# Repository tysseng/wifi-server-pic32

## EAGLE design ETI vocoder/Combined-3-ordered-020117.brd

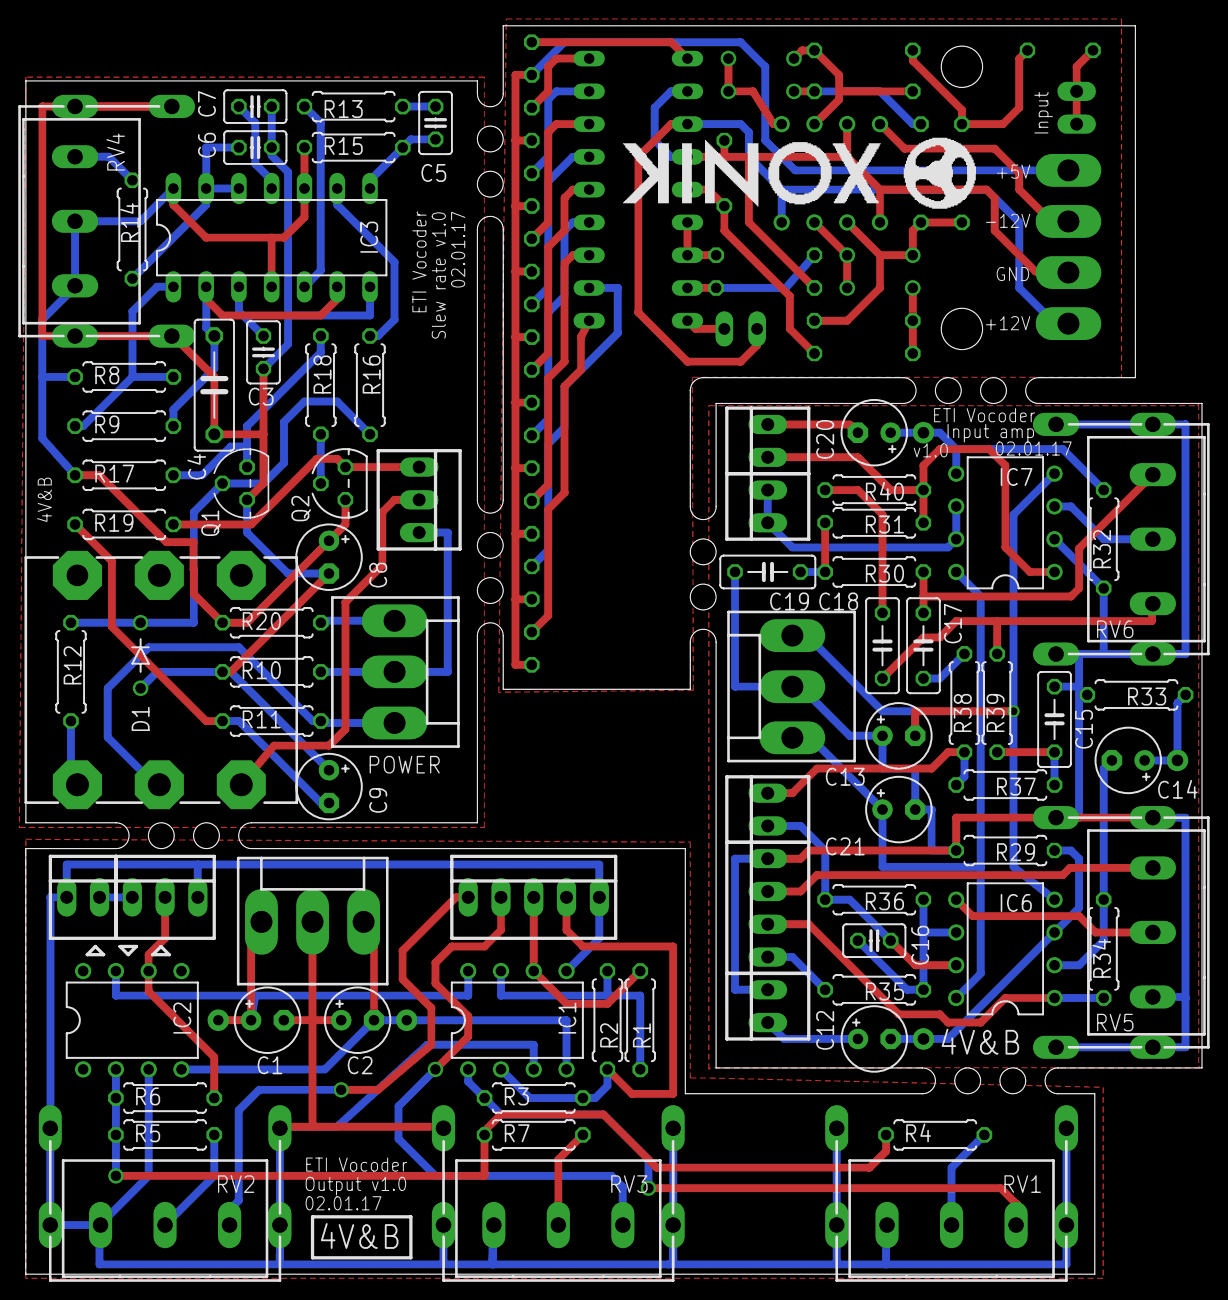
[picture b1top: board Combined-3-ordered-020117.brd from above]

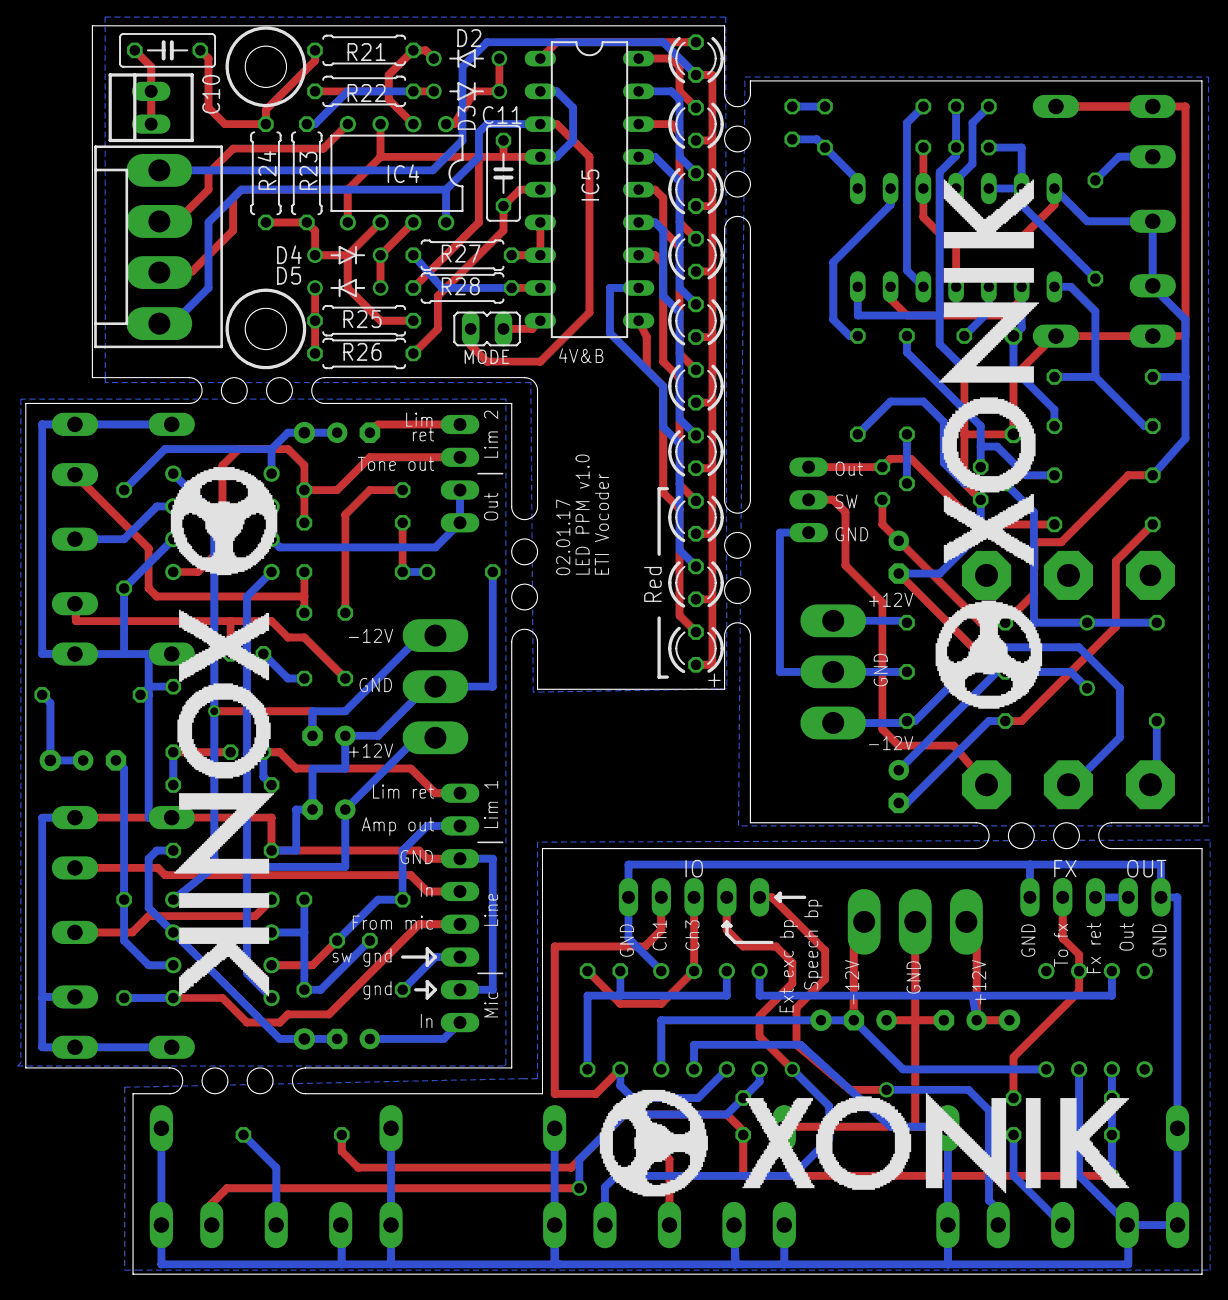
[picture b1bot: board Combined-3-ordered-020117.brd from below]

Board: 2 copper layers, 91.2 x 96.8 mm, 107 parts (29 on the bottom side), 88 nets.

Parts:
C1, C2: 1uF; E2,5-5
C3, C7: 10n; C025-025X050
C4: 33n; C075-032X103
C5: 100p; C025-025X050
C6: 560p; C025-025X050
C8, C9, C14: 22u; E2,5-5
C10, C15, C19: 220n; C050-025X075
C11: 470n; C050-025X075
C12, C20: 1u; E2,5-5
C13, C21: 22u/25V; E2,5-5
C16: 68p; C025-025X050
C17, C18: 2n2; C050-025X075
CN1: NMJ6HCD2
D1: 1N4148; DO35-5J
D2, D3, D4, D5: 1N4148DOJ35-5; DO35-5J
IC1, IC7: LM1458N; DIL08
IC2: LM741P; DIL08
IC3: LM556N; DIL14
IC4: TL082P; DIL08
IC5: LM3915N; DIL18
IC6: LM4558N; DIL08
IN: 22-23-2021
J1: 22-23-2031
LED1, LED2, LED3, LED4, LED5, LED6, LED7, LED8, LED9, LED10: LED3MM
LIM1, LIM2: 22-23-2021
LINE: 22-23-2041
MIC: 22-23-2021
MODE: JP1
OUT: 22-23-2021
POWER, POWER2: KK-156-3
POWER1: KK-156-4
Q1: 2N3904; TO92
Q2: 2N3906; TO92
R1, R2, R4, R5, R6, R7, R34: 22k; 0207/7
R3: 33k; 0207/7
R8: 15k; 0207/7
R9, R14, R17, R19: 2k2; 0207/7
R10, R20: 47R; 0207/7
R11: 220R; 0207/7
R12: 470R; 0207/7
R13, R26: 1k; 0207/7
R15, R16, R18: 10k; 0207/7
R21, R22, R23, R29, R32, R36: 100k; 0207/7
R24, R25: 200k; 0207/7
R27: 680R; 0207/7
R28: 150R; 0207/7
R30, R39: 47k; 0207/7
R31, R37: 1k5; 0207/7
R33: 470R/5k6; 0207/7
R35: 11k; 0207/7
R38, R40: 51k; 0207/7
RV1, RV2, RV3, RV5: 10k log; POT16_W_BRACKET
RV4: 1M log; POT16_W_BRACKET
RV6: 47k lin; POT16_W_BRACKET
X1: KK-156-3
X2: 22-23-2051
X3: 22-23-2021
X4: 22-23-2031

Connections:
0V: C3.1, C4.2, C6.1, C7.2, C8.-, C9.+, D1.A, IC3.7, Q1.3, R10.1, RV4.M1, RV4.M2, RV4.M3, RV4.M4
+5V: LED1.A, LED2.A, LED3.A, LED4.A, LED5.A, LED6.A, LED7.A, LED8.A, LED9.A, LED10.A, POWER1.4
+11V: C8.+, IC3.4, IC3.10, IC3.14, Q2.3, R8.2, R15.1, R17.2, R20.1, RV4.1E, RV4.1S
+12V: C1.+, IC1.8, IC2.7, X1.1
+12V1: POWER.1, R20.2
+12V2: IC4.8, IC5.3, MODE.2, POWER1.1
+12V3: C21.+, IC6.8, IC7.8, POWER2.1
-11V: C9.-, R11.1, R19.2
-12V: C2.-, IC1.4, IC2.4, X1.3
-12V1: CN1.R, POWER.3, R11.2
-12V2: IC4.4, POWER1.3
-12V3: C13.-, IC6.4, IC7.4, POWER2.3
AMP_OUT: C16.2, IC6.7, LIM1.1, R36.2
BUFFER_IN: C20.-, LIM2.2
CH1-2-4: IC1.2, R2.2, R3.1, X2.4
CH3-5-7: IC1.6, R1.1, X2.3
EXT_EXCIT: RV3.1E, X2.2
FROM_V/UV_SWITCH: CN1.T, X4.2
FX_RETURN: J1.1, X3.2
GND: C1.-, C2.+, IC1.3, IC1.5, IC2.3, J1.3, RV1.1A, RV1.M1, RV1.M2, RV1.M3, RV1.M4, RV2.1A, RV2.M1, RV2.M2, RV2.M3, RV2.M4, RV3.1A, RV3.M1, RV3.M2, RV3.M3, RV3.M4, X1.2, X2.5, X3.1
GND1: POWER.2, R10.2, X4.3
GND2: C11.1, IC4.3, IC4.5, IC5.2, IC5.4, POWER1.2, R28.1
GND3: C13.+, C15.2, C19.1, C21.-, IC7.2, LINE.4, MIC.2, POWER2.2, R29.1, R32.1, R33.1, RV5.1A, RV5.M1, RV5.M2, RV5.M3, RV5.M4, RV6.M1, RV6.M2, RV6.M3, RV6.M4
LINE_IN: LINE.3, RV5.1E
MIC_IN: C12.+, MIC.1
MIC_OUT: IC6.1, LINE.2, R34.1
MIX: IC2.6, J1.2, R6.2
MODE: IC5.9, MODE.1
unnamed: R4.1, RV1.1S
unnamed: C5.2, IC3.8, R15.2
unnamed: IC1.7, R1.2, R2.1
unnamed: C4.1, IC3.2, IC3.6, R9.2
unnamed: C7.1, IC3.11
unnamed: IC1.1, R3.2, RV1.1E
unnamed: R7.1, RV3.1S
unnamed: IC2.2, R4.2, R5.1, R6.1, R7.2
unnamed: IC3.9, R16.1
unnamed: R5.2, RV2.1S
unnamed: C6.2, IC3.12, IC3.13, R14.1
unnamed: C5.1, R13.2
unnamed: IC3.5, R13.1
unnamed: IC3.1, R8.1, R9.1
unnamed: R14.2, RV4.1A
unnamed: C3.2, IC3.3
unnamed: D1.C, Q1.2, R12.2, R16.2
unnamed: Q1.1, R17.1, R18.2
unnamed: Q2.2, R18.1
unnamed: CN1.S, R12.1
unnamed: D3.A, R22.1, R23.2
unnamed: D2.C, IC4.2, R21.1, R22.2
unnamed: D2.A, D3.C, IC4.1
unnamed: D4.A, IC4.6, R23.1, R24.1, R25.2
unnamed: D5.C, R25.1, R26.1
unnamed: C10.2, R21.2, R24.2
unnamed: D4.C, D5.A, IC4.7
unnamed: C11.2, IC5.5, R26.2
unnamed: IC5.6, IC5.7, R27.2
unnamed: IC5.1, LED1.K
unnamed: IC5.18, LED2.K
unnamed: IC5.17, LED3.K
unnamed: IC5.16, LED4.K
unnamed: IC5.15, LED5.K
unnamed: IC5.14, LED6.K
unnamed: IC5.13, LED7.K
unnamed: IC5.12, LED8.K
unnamed: IC5.11, LED9.K
unnamed: IC5.10, LED10.K
unnamed: C10.1, IN.1, IN.2
unnamed: IC5.8, R27.1, R28.2
unnamed: C12.-, IC6.3, R29.2
unnamed: C14.-, IC6.2, R34.2
unnamed: C14.+, R33.2
unnamed: C16.1, IC6.6, R35.2, R36.1
unnamed: C15.1, R37.2, R39.2
unnamed: C18.1, R39.1, RV6.1A
unnamed: C17.2, R30.1, RV6.1E
unnamed: C17.1, R38.2
unnamed: C18.2, R40.1
unnamed: C19.2, R30.2, R31.1
unnamed: C20.+, IC7.5, R32.2
unnamed: IC7.3, RV6.1S
unnamed: IC6.5, RV5.1S
OUT: Q2.1, R19.1, X4.1
OUT1: IC7.6, IC7.7, OUT.1, OUT.2
SPEECH: RV2.1E, X2.1
SWITCHED_GND: LINE.1, R35.1
TONE_IN: LIM1.2, R37.1, R38.1
TONE_OUT: IC7.1, LIM2.1, R31.2, R40.2

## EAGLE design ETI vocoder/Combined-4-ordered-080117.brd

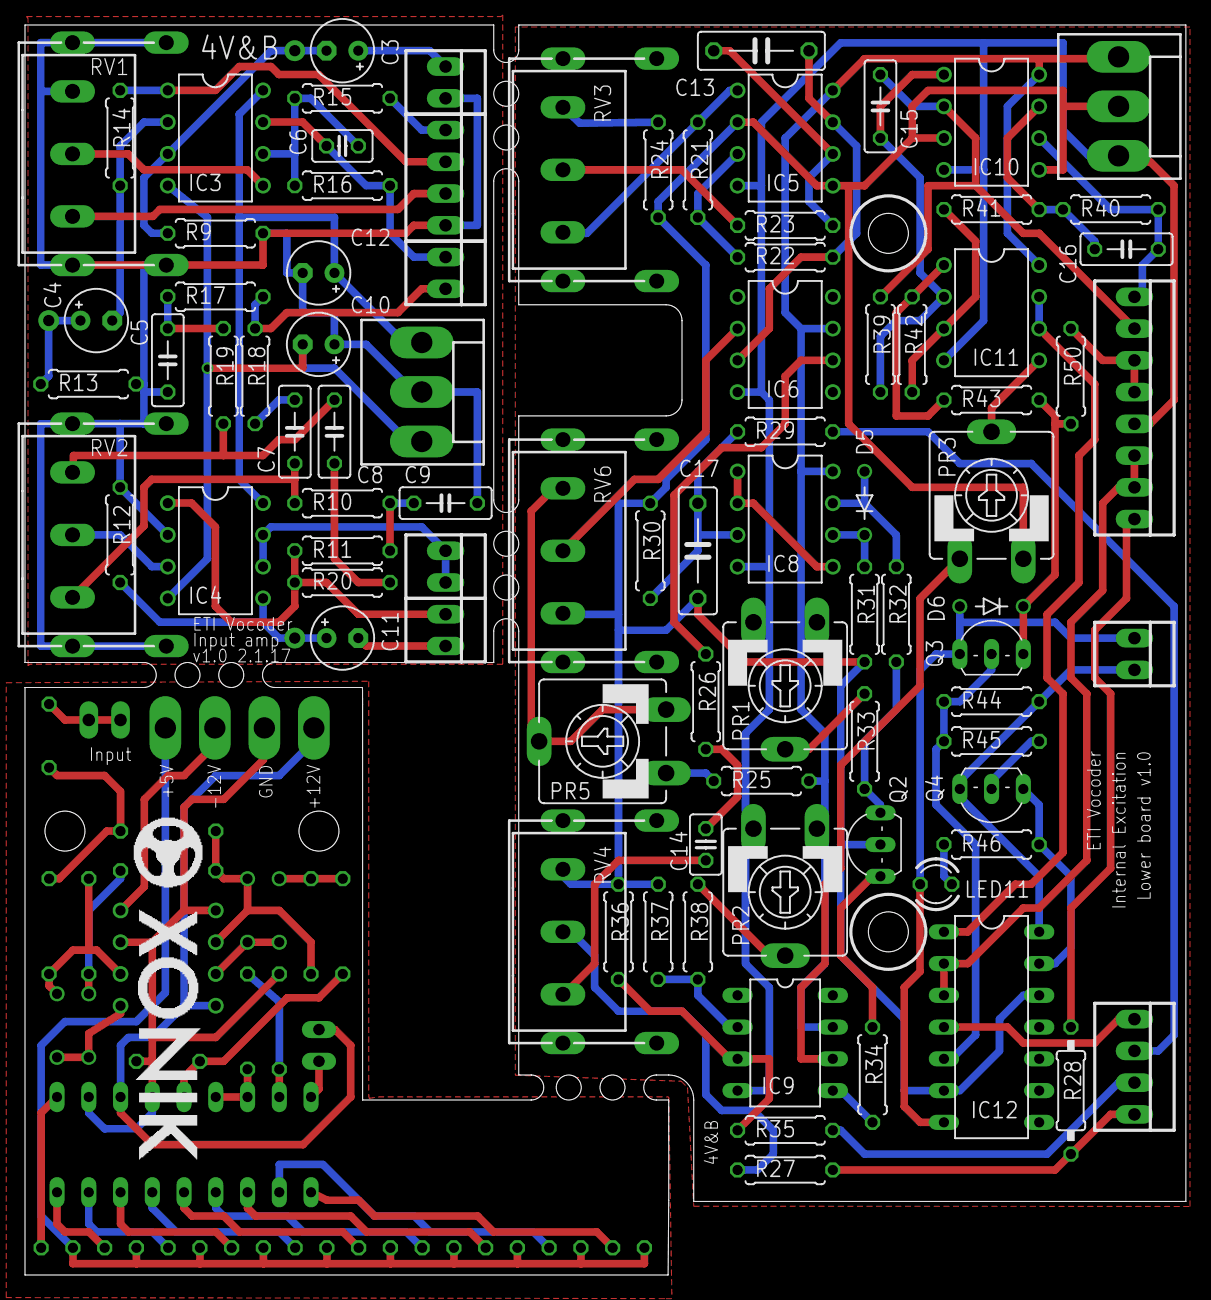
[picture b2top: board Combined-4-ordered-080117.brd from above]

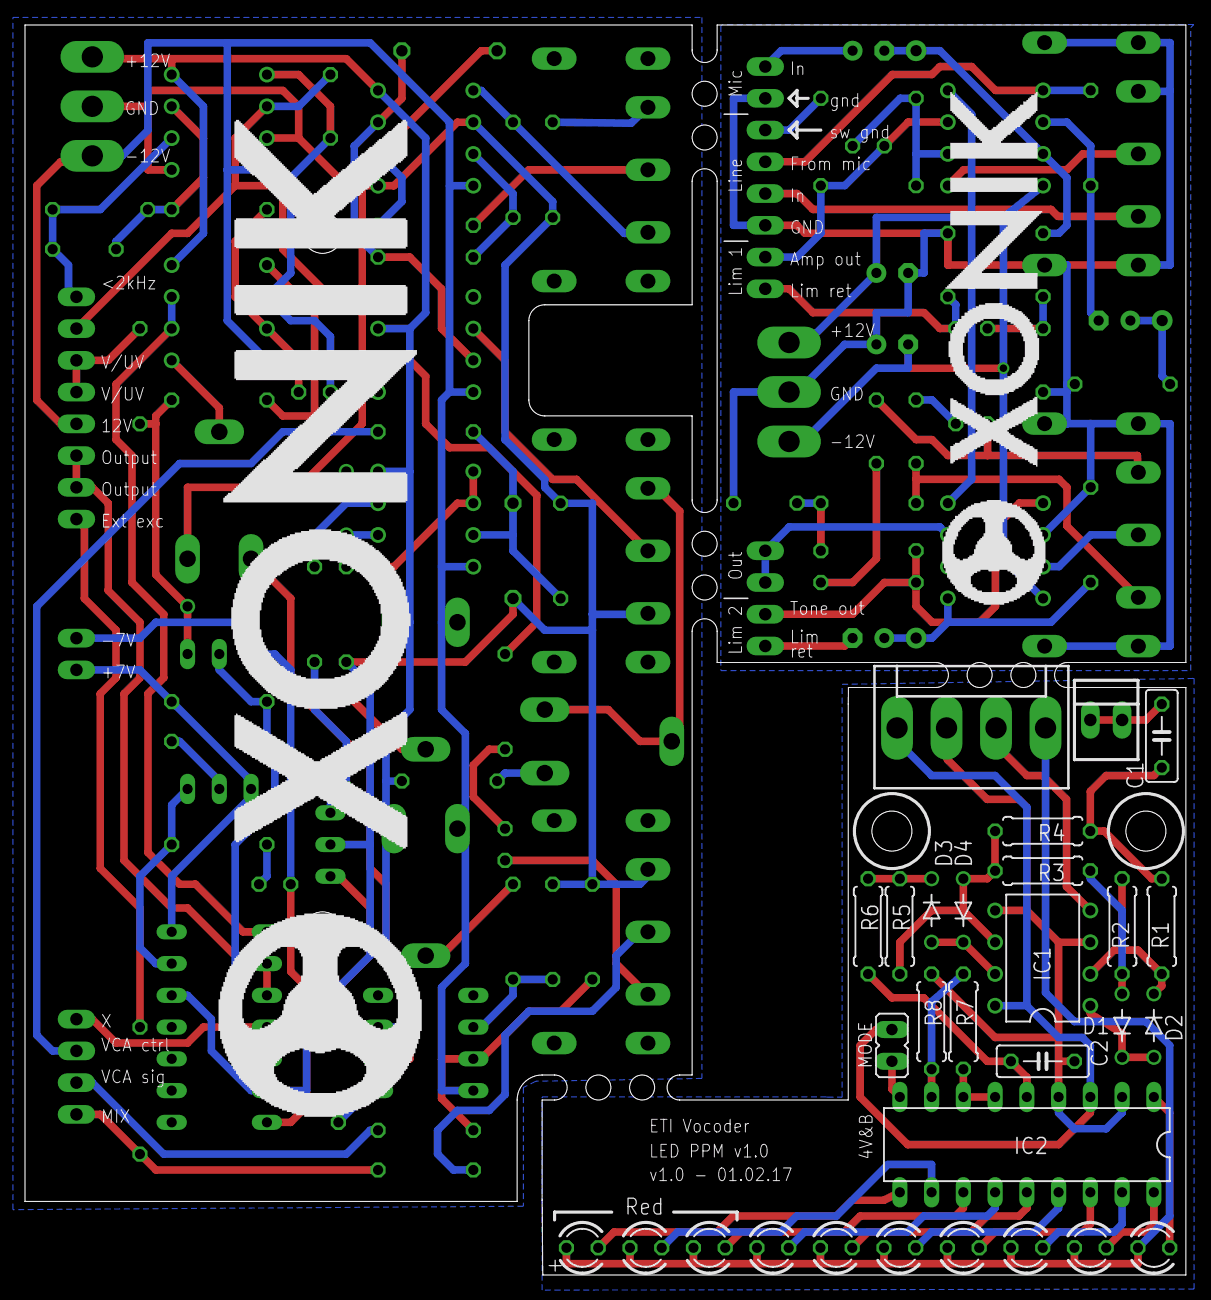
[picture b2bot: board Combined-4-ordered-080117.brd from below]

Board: 2 copper layers, 92.9 x 100.0 mm, 117 parts (29 on the bottom side), 101 nets.

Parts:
BOARD2: 22-23-2041
BOARD2-PWR: 22-23-2021
C1, C5, C9, C15: 220n; C050-025X075
C2: 470n; C050-025X075
C3, C11: 1u; E2,5-5
C4: 22u; E2,5-5
C6: 68p; C025-025X050
C7, C8: 2n2; C050-025X075
C10, C12: 22u/25V; E2,5-5
C13, C17: 100n; C075-032X103
C14: 10n; C025-025X050
C16: 1u0; C050-025X075
D1, D2, D3, D4: 1N4148DOJ35-5; DO35-5J
D5, D6: 1N4148; DO35-5J
IC1, IC8: TL082P; DIL08
IC2: LM3915N; DIL18
IC3: LM4558N; DIL08
IC4, IC5, IC10, IC11: LM1458N; DIL08
IC6: TL081P; DIL08
IC9: CA3080E; DIL08
IC12: 4016N; DIL14
IN: 22-23-2021
IO: 22-23-2081
LED1, LED2, LED3, LED4, LED5, LED6, LED7, LED8, LED9, LED10, LED11: LED3MM
LIM1, LIM2: 22-23-2021
LINE: 22-23-2041
MIC: 22-23-2021
MODE: JP1
OUT: 22-23-2021
POWER: KK-156-4
POWER1, POWER2: KK-156-3
PR1, PR2: 100k; CA9V
PR3: 220k; CA9V
PR5: 2k2; CA9V
Q2, Q4: BC212L; TO92-CBE
Q3: BC182L; TO92-ECB
R1, R2, R3, R9, R12, R16: 100k; 0207/7
R4, R5: 200k; 0207/7
R6, R41: 1k; 0207/7
R7: 680R; 0207/7
R8: 150R; 0207/7
R10, R19, R27, R35, R39, R43: 47k; 0207/7
R11, R17, R36, R37, R46: 1k5; 0207/7
R13: 470R/5k6; 0207/7
R14, R32: 22k; 0207/7
R15, R25: 11k; 0207/7
R18, R20: 51k; 0207/7
R21, R29, R34, R40, R44, R45, R50: 10k; 0207/7
R22: 5k6; 0207/7
R23: 18k; 0207/7
R24: 560R; 0207/7
R26: 150k; 0207/7
R28: 47k; 0207/10
R30, R42: 1M; 0207/7
R31: 3k9; 0207/7
R33, R38: 470k; 0207/7
RV1, RV3, RV4: 10k log; POT16_W_BRACKET
RV2: 47k lin; POT16_W_BRACKET
RV6: 10k; POT16_W_BRACKET

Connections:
2KHZ: C16.1, IC10.6, IO.1, R40.1
4KHZ: C15.1, IC10.2, IO.2, R39.1
+5V: LED1.A, LED2.A, LED3.A, LED4.A, LED5.A, LED6.A, LED7.A, LED8.A, LED9.A, LED10.A, POWER.4
+12V: IC1.8, IC2.3, MODE.2, POWER.1
+12V1: C12.+, IC3.8, IC4.8, POWER1.1
+12V2: IC5.8, IC6.7, IC8.8, IC9.7, IC10.8, IC11.8, POWER2.1, PR1.A, PR2.A, R25.1
-12V: IC1.4, POWER.3
-12V1: C10.-, IC3.4, IC4.4, POWER1.3
-12V2: IC5.4, IC6.4, IC8.4, IC9.4, IC10.4, IC11.4, IO.5, POWER2.3, PR1.E, PR2.E
AMP_OUT: C6.2, IC3.7, LIM1.1, R16.2
BOARD2_MIX: BOARD2.4, R27.1, R28.1
BUFFER_IN: C11.-, LIM2.2
EXT_EXCIT: IO.8, R28.2
GND: C2.1, IC1.3, IC1.5, IC2.2, IC2.4, POWER.2, R8.1
GND1: C5.2, C9.1, C10.+, C12.-, IC4.2, LINE.4, MIC.2, POWER1.2, R9.1, R12.1, R13.1, RV1.1A, RV1.M1, RV1.M2, RV1.M3, RV1.M4, RV2.M1, RV2.M2, RV2.M3, RV2.M4
GND2: C17.1, IC5.2, IC5.5, IC10.3, IC10.5, IC12.6, IC12.12, POWER2.2, PR3.E, Q2.B, R24.2, R30.2, R31.2, R36.2, R37.2, RV4.1A, RV6.1E
LINE_IN: LINE.3, RV1.1E
MIC_IN: C3.+, MIC.1
MIC_OUT: IC3.1, LINE.2, R14.1
MODE: IC2.9, MODE.1
unnamed: D1.A, R2.1, R3.2
unnamed: D2.C, IC1.2, R1.1, R2.2
unnamed: D1.C, D2.A, IC1.1
unnamed: D4.A, IC1.6, R3.1, R4.1, R5.2
unnamed: D3.C, R5.1, R6.1
unnamed: C1.2, R1.2, R4.2
unnamed: D3.A, D4.C, IC1.7
unnamed: C2.2, IC2.5, R6.2
unnamed: IC2.6, IC2.7, R7.2
unnamed: C3.-, IC3.3, R9.2
unnamed: IC2.1, LED1.K
unnamed: IC2.18, LED2.K
unnamed: IC2.17, LED3.K
unnamed: IC2.16, LED4.K
unnamed: IC2.15, LED5.K
unnamed: IC2.14, LED6.K
unnamed: IC2.13, LED7.K
unnamed: IC2.12, LED8.K
unnamed: IC2.11, LED9.K
unnamed: IC2.10, LED10.K
unnamed: IC2.8, R7.1, R8.2
unnamed: C1.1, IN.1, IN.2
unnamed: C4.-, IC3.2, R14.2
unnamed: C4.+, R13.2
unnamed: C6.1, IC3.6, R15.2, R16.1
unnamed: C5.1, R17.2, R19.2
unnamed: C8.1, R19.1, RV2.1A
unnamed: C7.2, R10.1, RV2.1E
unnamed: C7.1, R18.2
unnamed: C8.2, R20.1
unnamed: C9.2, R10.2, R11.1
unnamed: C11.+, IC4.5, R12.2
unnamed: IC4.3, RV2.1S
unnamed: IC3.5, RV1.1S
unnamed: IC5.3, R21.1, R22.1
unnamed: IC5.1, R21.2, RV3.1E
unnamed: R23.2, RV3.1S
unnamed: C13.1, IC5.6, R23.1
unnamed: R24.1, RV3.1A
unnamed: C13.2, IC5.7, IC6.3, R22.2
unnamed: IC6.2, RV6.1S
unnamed: PR5.A, R25.2
unnamed: PR5.E, PR5.S, RV6.1A
unnamed: IC6.6, R26.2
unnamed: C14.2, R26.1
unnamed: C14.1, RV4.1E
unnamed: R27.2, RV4.1S
unnamed: C15.2, IC10.1, IC11.2, R39.2
unnamed: C16.2, IC10.7, R40.2, R41.1
unnamed: IC11.3, R41.2, R42.1
unnamed: IC11.1, R42.2, R43.1
unnamed: IC12.5, Q3.C, R44.1, R45.2
unnamed: Q4.B, R45.1
unnamed: D6.C, Q3.B, R43.2, R50.2
unnamed: IC12.13, Q4.C, R46.1
unnamed: LED11.A, R46.2
unnamed: IC9.3, R35.1, R36.1
unnamed: IC9.2, R37.1, R38.1
unnamed: PR2.S, R38.2
unnamed: IC9.5, R34.2
unnamed: Q2.E, R32.1, R33.2
unnamed: PR1.S, R33.1
unnamed: IC11.5, PR3.S
unnamed: IC11.6, IC11.7, IC12.1
unnamed: D5.A, IC8.7, R32.2
unnamed: IC8.1, IC8.2, IC8.5
unnamed: D5.C, IC8.6, R31.1
unnamed: C17.2, IC8.3, R29.2, R30.1
unnamed: IC9.6, PR3.A
unnamed: Q2.C, R34.1
OUT: IC4.6, IC4.7, OUT.1, OUT.2
OUT1: IC12.2, IC12.3, IO.6, IO.7
SWITCHED_GND: LINE.1, R15.1
TONE_IN: LIM1.2, R17.1, R18.1
TONE_OUT: IC4.1, LIM2.1, R11.2, R20.2
VCA_CTRL: BOARD2.2, R29.1
VCA_SIGNAL: BOARD2.3, R35.2
VDD: BOARD2-PWR.2, IC12.14, Q4.E, R44.2
VSS: BOARD2-PWR.1, D6.A, IC12.7, LED11.K, Q3.E
V_UV_ON_OFF: IO.3, IO.4, R50.1
X: BOARD2.1, IC12.4

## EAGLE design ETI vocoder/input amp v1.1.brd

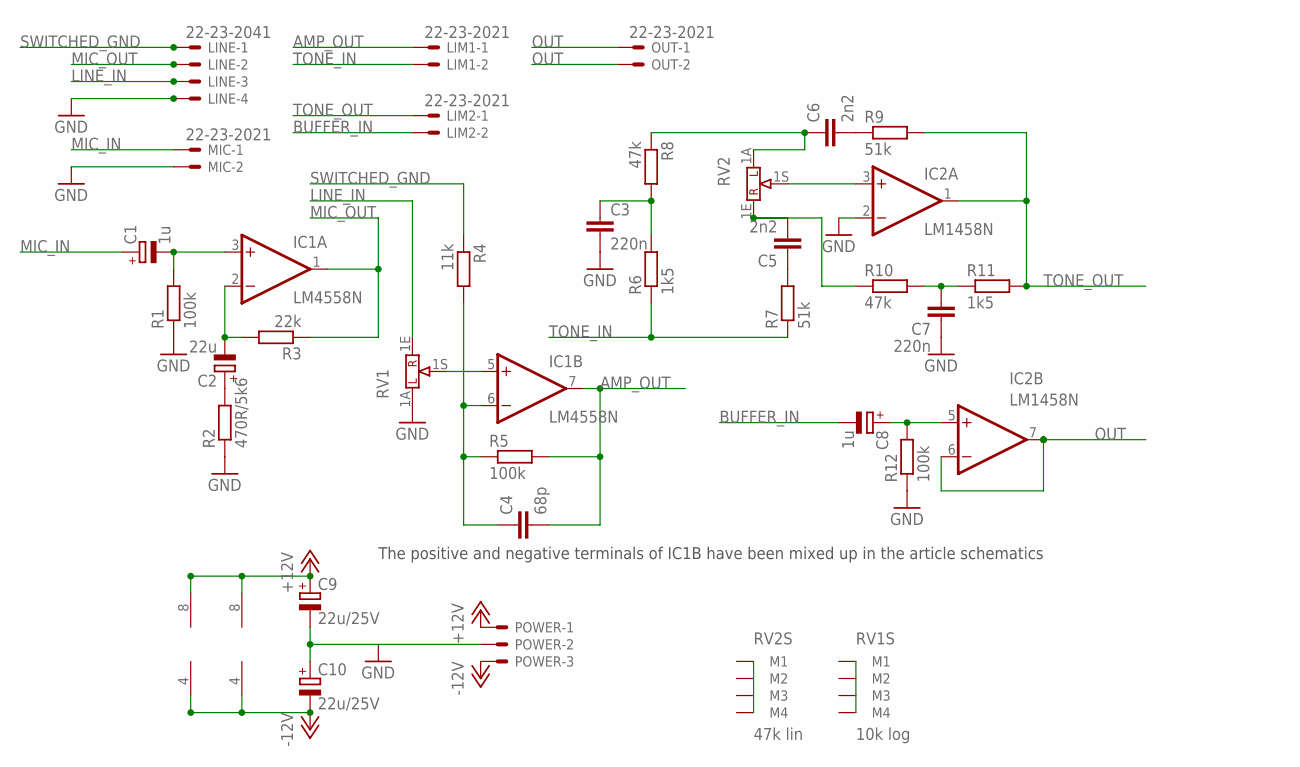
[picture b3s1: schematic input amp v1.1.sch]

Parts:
C1, C8: 1u; E2,5-5
C2: 22u; E2,5-5
C3, C7: 220n; C050-030X075
C4: 68p; C025-025X050
C5, C6: 2n2; C050-030X075
C9, C10: 22u/25V; E2,5-5
IC1: LM4558N; DIL08
IC2: LM1458N; DIL08
LIM1, LIM2: 22-23-2021
LINE: 22-23-2041
MIC: 22-23-2021
OUT: 22-23-2021
POWER: KK-156-3
R1, R5, R12: 100k; 0207/7
R2: 470R/5k6; 0207/7
R3: 22k; 0207/7
R4: 11k; 0207/7
R6, R11: 1k5; 0207/7
R7, R9: 51k; 0207/7
R8, R10: 47k; 0207/7
RV1: 10k log; POT16_W_BRACKET
RV2: 47k lin; POT16_W_BRACKET

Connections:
+12V: C9.+, IC1.8 (V+), IC2.8 (V+), POWER.1
-12V: C10.-, IC1.4 (V-), IC2.4 (V-), POWER.3
AMP_OUT: C4.2, IC1.7 (OUT), LIM1.1, R5.2
BUFFER_IN: C8.-, LIM2.2
GND: C3.2, C7.1, C9.-, C10.+, IC2.2 (-IN), LINE.4, MIC.2, POWER.2, R1.1, R2.1, R12.1, RV1.1A
LINE_IN: LINE.3, RV1.1E
MIC_IN: C1.+, MIC.1
MIC_OUT: IC1.1 (OUT), LINE.2, R3.1
unnamed: C1.-, IC1.3 (+IN), R1.2
unnamed: C2.-, IC1.2 (-IN), R3.2
unnamed: IC2.3 (+IN), RV2.1S
unnamed: C2.+, R2.2
unnamed: IC1.5 (+IN), RV1.1S
unnamed: C4.1, IC1.6 (-IN), R4.2, R5.1
unnamed: C3.1, R6.2, R8.2
unnamed: C6.1, R8.1, RV2.1A
unnamed: C5.2, R10.1, RV2.1E
unnamed: C5.1, R7.2
unnamed: C6.2, R9.1
unnamed: C7.2, R10.2, R11.1
unnamed: C8.+, IC2.5 (+IN), R12.2
OUT: IC2.6 (-IN), IC2.7 (OUT), OUT.1, OUT.2
SWITCHED_GND: LINE.1, R4.1
TONE_IN: LIM1.2, R6.1, R7.1
TONE_OUT: IC2.1 (OUT), LIM2.1, R9.2, R11.2

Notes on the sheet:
The positive and negative terminals of IC1B have been mixed up in the article schematics

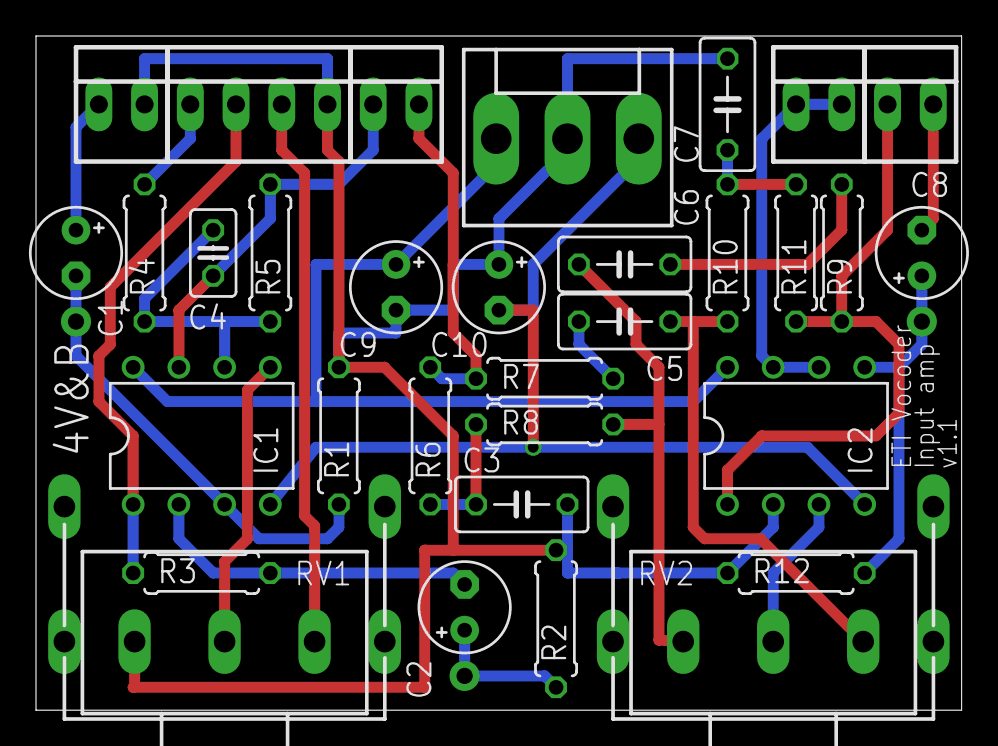
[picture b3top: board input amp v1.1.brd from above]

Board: 2 copper layers, 51.4 x 37.5 mm, 32 parts (0 on the bottom side), 25 nets.

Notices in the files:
parts and their libraries:
audio: Copyright (C) 2008, Bob Starr
